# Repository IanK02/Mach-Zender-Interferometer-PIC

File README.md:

# Mach-Zender Interferometer Photonic Integrated Circuit

A photonic integrated circuit designed in Python with [gdsfactory](https://github.com/gdsfactory/gdsfactory), laid out in [KLayout](https://www.klayout.de/), with a companion PCB designed in [KiCad](https://www.kicad.org/).

Chip implements four Mach-Zender-Interferometers of varying lengths, with accompanying chip providing all required electrical usage and testing hardware.

## Gallery

| Die Layout | PCB 3D View |
|:---:|:---:|
|  |  |
| **PCB 2D View** | **Circuit Schematic** |
|  |  |

## Features

- Four MZIs with thermal phase shifters
- 12V barrel jack connector for power
- Glue-in spot on PCB for inserting MZI chip

## PDK

This design uses gdsfactory's open-source generic PDK, so the whole layout can be regenerated and freely shared. Layer numbers and components are generic and not tied to any commercial foundry process.

## Tools
- **gdsfactory**: parametric layout in Python
- **KLayout**: layout viewing and rendering
- **KiCad**: schematic and PCB design

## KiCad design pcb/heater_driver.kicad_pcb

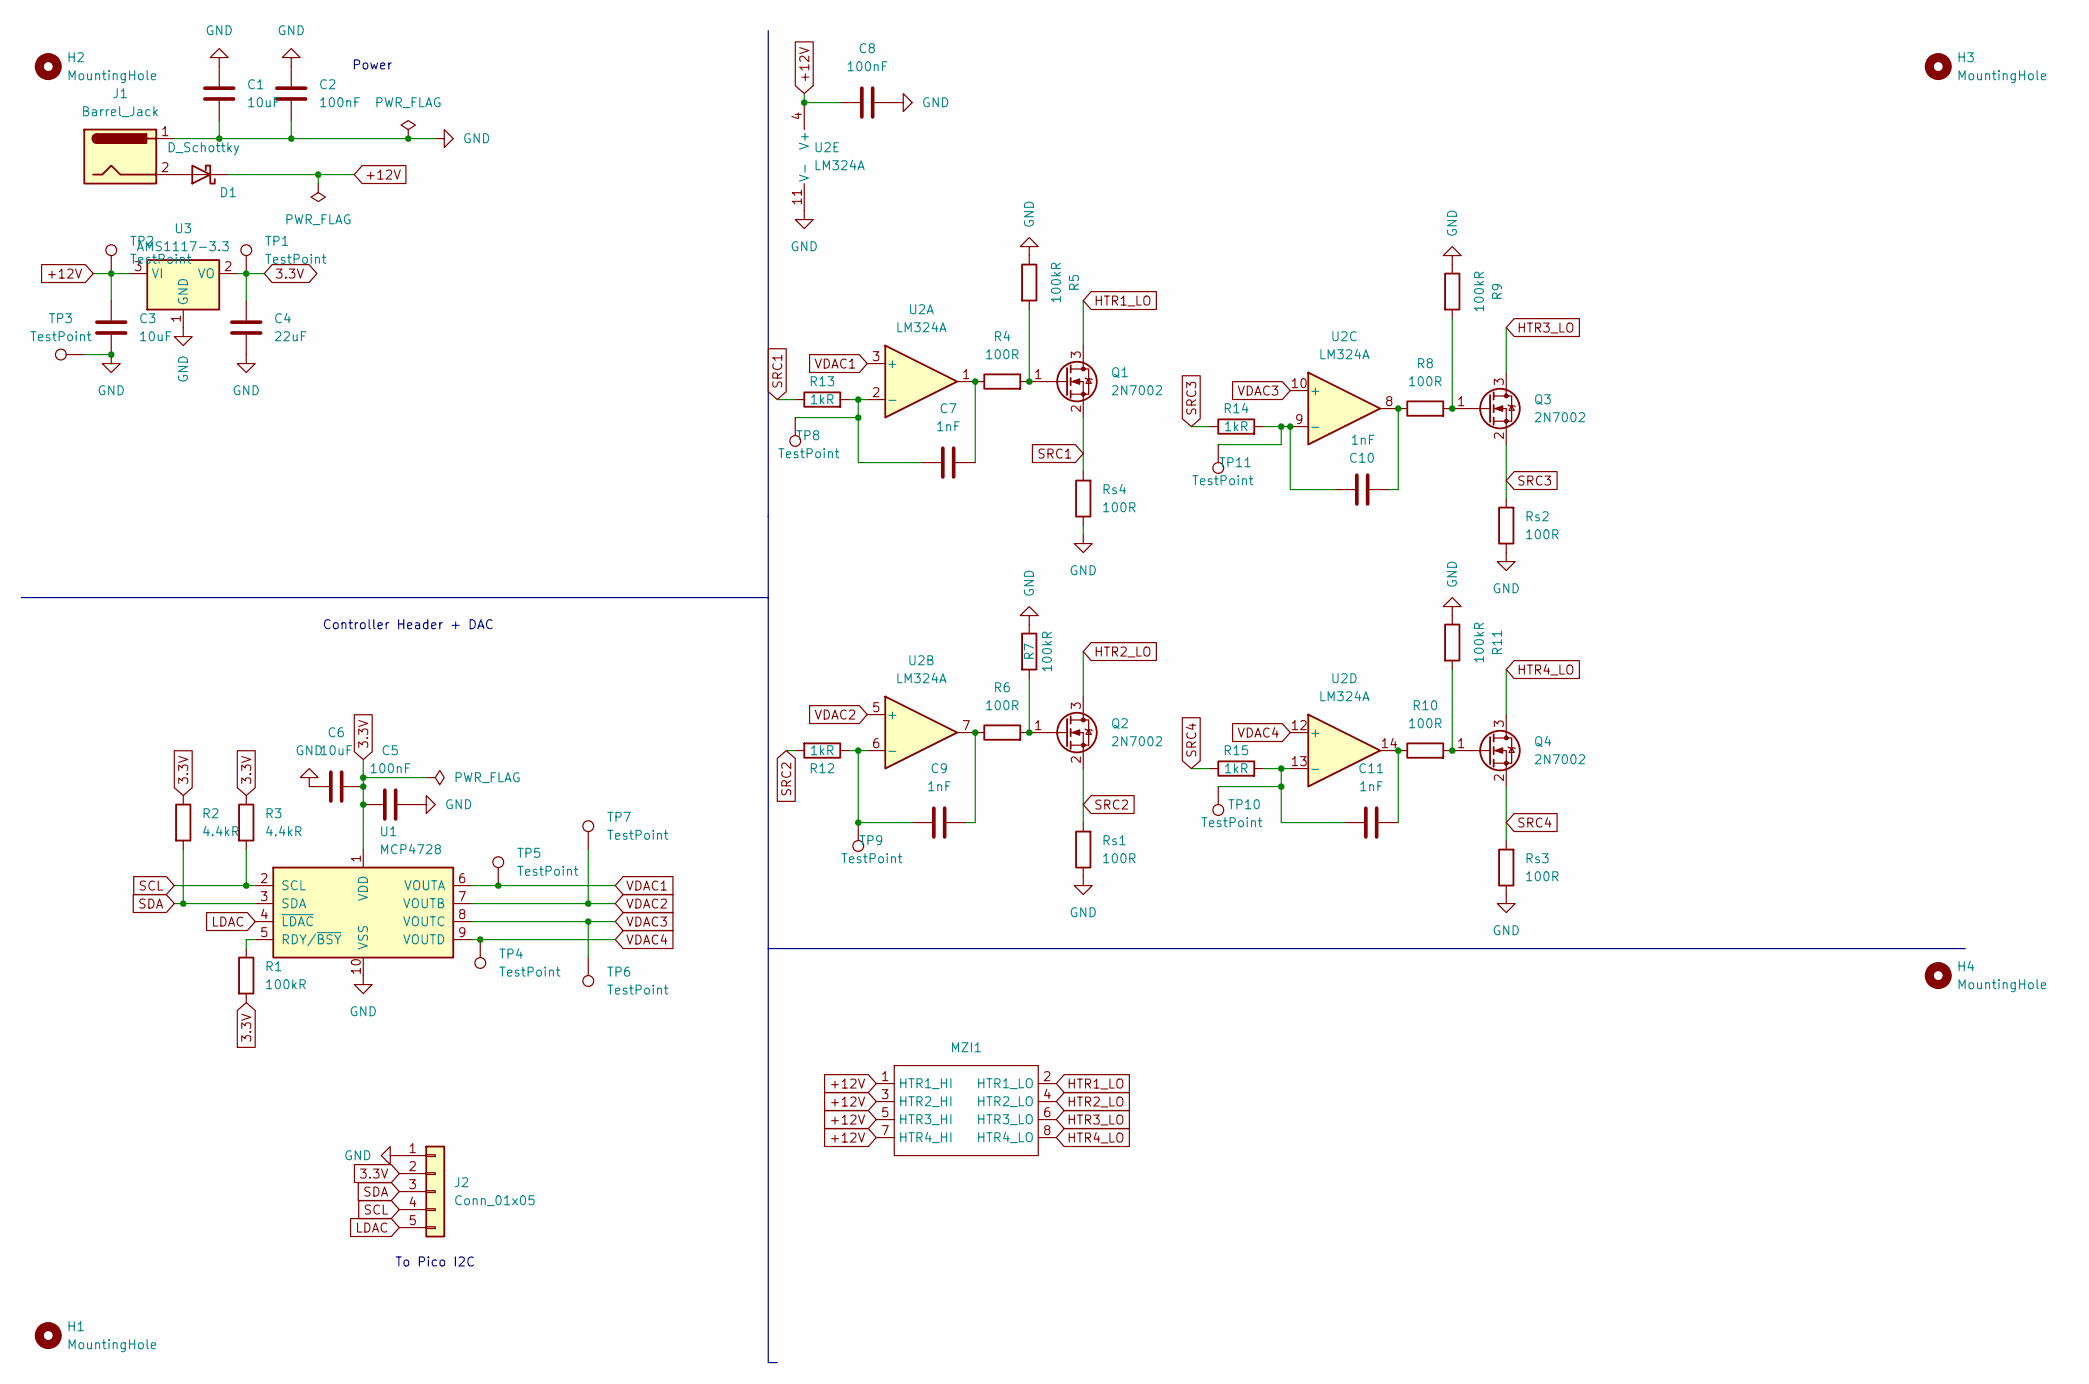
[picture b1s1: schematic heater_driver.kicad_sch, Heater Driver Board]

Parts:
C1, C3, C6: 10uF; C_0805_2012Metric; MPN GMC04X5R106M10NT; LCSC C1691
C2, C5, C8: 100nF; C_0805_2012Metric; MPN C0603C104K5RACTU; LCSC C1525
C4: 22uF; C_0805_2012Metric; MPN GMC04X5R226M6R3NT; LCSC C1859
C7, C9, C10, C11: 1nF; C_0805_2012Metric; MPN 0805B102K101BD; LCSC C1523
D1: D_Schottky; D_SOD-123; MPN BAT54LT1G; LCSC C82544
H1, H2, H3, H4: MountingHole; MountingHole_3.2mm_M3
J1: Barrel_Jack; BarrelJack_SwitchcraftConxall_RAPC10U_Horizontal; MPN PJ-037A
J2: Conn_01x05; PinHeader_1x05_P2.54mm_Vertical
MZI1: PIC_MZI_DIE
Q1, Q2, Q3, Q4: 2N7002; SOT-23TO-236_318-08_ONS; MPN 2N7002
R1, R5, R7, R9, R11: 100kR; R_0805_2012Metric; MPN CR0603FB100KS1
R2, R3: 4.4kR; R_0805_2012Metric; MPN RN73H1JTTD3442F100
R4, R6, R8, R10: 100R; R_0805_2012Metric; MPN CR0402JC100RS1
R12, R13, R14, R15: 1kR; R_0805_2012Metric; MPN ERJ-2RKF1001X
Rs1, Rs2, Rs3, Rs4: 100R; R_0805_2012Metric; MPN CR0402JC100RS1
TP1, TP2, TP3, TP4, TP5, TP6, TP7, TP8, TP9, TP10, TP11: TestPoint; TestPoint_Pad_D1.5mm; MPN 36-5006-ND
U1: MCP4728; MSOP10_MC_MCH; MPN MCP4728T-E/UN
U2: LM324A; M14A; MPN LM324DR; LCSC C5288549
U3: AMS1117-3.3; SOT-223-3_TabPin2; MPN AMS1117-3.3 SOT-223

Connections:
3.3V: C4.1, C5.1, C6.2, J2.2, R1.2, R2.1, R3.1, TP1.1 (1_1), U1.1 (VDD), U3.2 (VO)
+12V: C3.1, C8.1, D1.1 (K), MZI1.1 (HTR1_HI), MZI1.3 (HTR2_HI), MZI1.5 (HTR3_HI), MZI1.7 (HTR4_HI), TP2.1 (1_1), U2.4 (V+), U3.3 (VI)
GND: C1.1, C1.2, C2.1, C2.2, C3.2, C4.2, C5.2, C6.1, C8.2, J1.1, J2.1, R5.1, R7.1, R9.1, R11.1, Rs1.1, Rs2.1, Rs3.1, Rs4.1, TP3.1 (1_1), U1.10 (VSS), U2.11 (V-), U3.1 (GND)
HTR1_LO: MZI1.2 (HTR1_LO), Q1.3 (D)
HTR2_LO: MZI1.4 (HTR2_LO), Q2.3 (D)
HTR3_LO: MZI1.6 (HTR3_LO), Q3.3 (D)
HTR4_LO: MZI1.8 (HTR4_LO), Q4.3 (D)
LDAC: J2.5, U1.4 (~LDAC)
unnamed: C7.2, R4.1, U2.1
unnamed: C9.2, R6.1, U2.7
unnamed: C10.1, R8.1, U2.8
unnamed: C11.2, R10.1, U2.14
unnamed: D1.2 (A), J1.2
unnamed: Q1.1 (G), R4.2, R5.2
unnamed: Q2.1 (G), R6.2, R7.2
unnamed: Q3.1 (G), R8.2, R9.2
unnamed: Q4.1 (G), R10.2, R11.2
unnamed: R1.1, U1.5 (RDY/~BSY)
unnamed: C7.1, R13.2, TP8.1 (1_1), U2.2 (-)
unnamed: C9.1, R12.1, TP9.1 (1_1), U2.6 (-)
unnamed: C10.2, R14.2, TP11.1 (1_1), U2.9 (-)
unnamed: C11.1, R15.2, TP10.1 (1_1), U2.13 (-)
SCL: J2.4, R3.2, U1.2 (SCL)
SDA: J2.3, R2.2, U1.3 (SDA)
SRC1: Q1.2 (S), R13.1, Rs4.2
SRC2: Q2.2 (S), R12.2, Rs1.2
SRC3: Q3.2 (S), R14.1, Rs2.2
SRC4: Q4.2 (S), R15.1, Rs3.2
VDAC1: TP5.1 (1_1), U1.6 (VOUTA), U2.3 (+)
VDAC2: TP7.1 (1_1), U1.7 (VOUTB), U2.5 (+)
VDAC3: TP6.1 (1_1), U1.8 (VOUTC), U2.10 (+)
VDAC4: TP4.1 (1_1), U1.9 (VOUTD), U2.12 (+)

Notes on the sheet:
Power
Controller Header + DAC
To Pico I2C

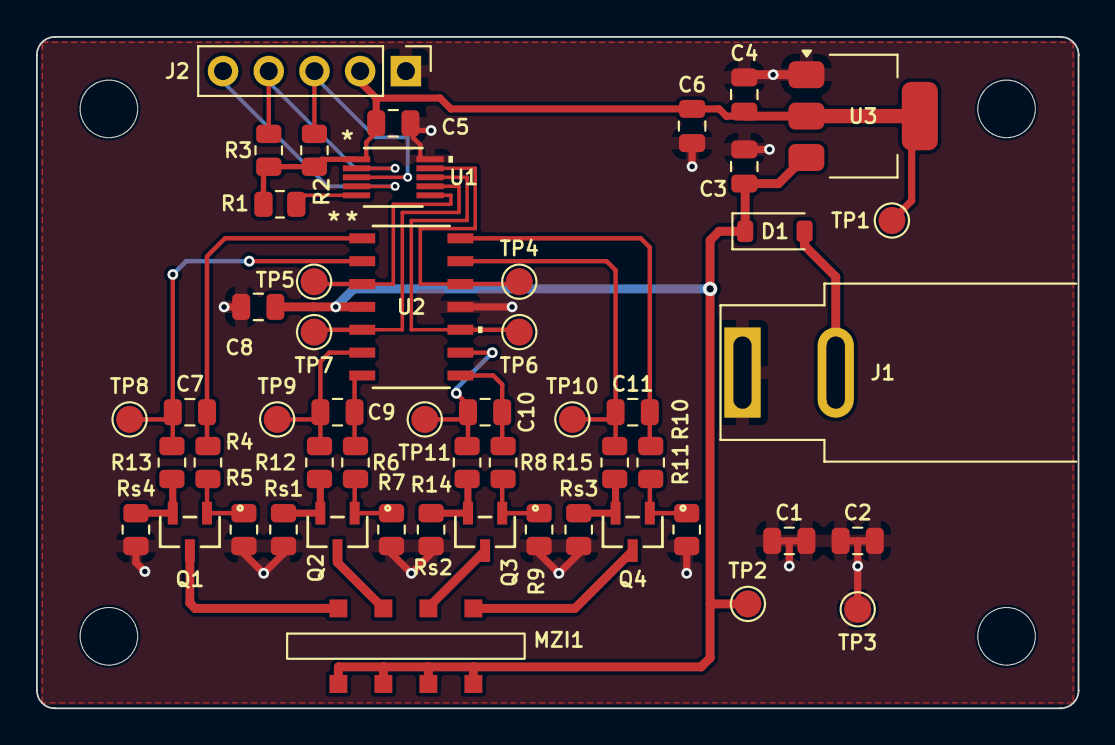
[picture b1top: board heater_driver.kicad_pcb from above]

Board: 2 copper layers, 57.9 x 37.3 mm, 56 parts (0 on the bottom side), 32 nets.
